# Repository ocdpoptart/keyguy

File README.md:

This entire thing has been a project to make a keyboard that had every quality I liked in one except for having a usb hub (I figured I could make one of those later). Unfortunately this entire thing has spiraled out of control and now I have even learned how to use this silly thing called GitHub. I want to cry.

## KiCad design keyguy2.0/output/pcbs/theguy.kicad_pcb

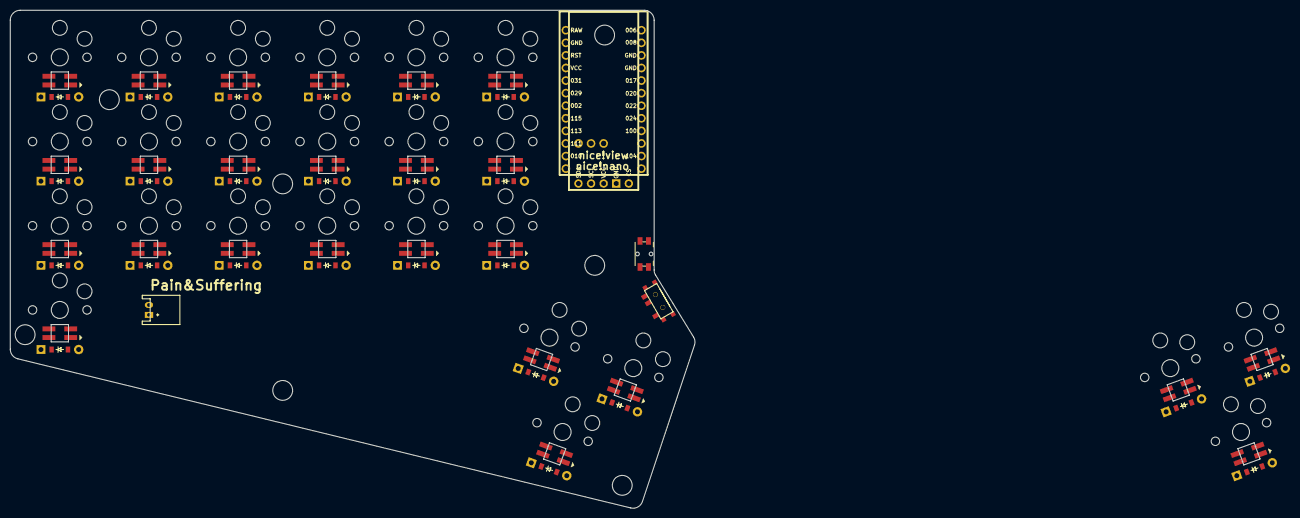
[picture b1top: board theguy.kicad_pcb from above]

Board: 2 copper layers, 255.0 x 100.5 mm, 80 parts (0 on the bottom side), 64 nets, no tracks yet.

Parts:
B1: Panasonic_EVQPUL_EVQPUC
D1, D2, D3, D4, D5, D6, D7, D8, D9, D10, D11, D12, D13, D14, D15, D16, D17, D18, D19, D20, D21, D22, D23, D24, D25: ComboDiode
JST1: JST_PH_S2B-PH-K_02x2.00mm_Angled
LED1, LED2, LED3, LED4, LED5, LED6, LED7, LED8, LED9, LED10, LED11, LED12, LED13, LED14, LED15, LED16, LED17, LED18, LED19, LED20, LED21, LED22, LED23, LED24, LED25: WS2812B
MCU1: nice_nano
S1, S2, S3, S4, S5, S6, S7, S8, S9, S10, S11, S12, S13, S14, S15, S16, S17, S18, S19, S20, S21, S22, S23, S24, S25: PG1350
T1: SPDT_C128955
niceView1: niceView; niceView_headers

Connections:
GND: B1.1, JST1.2, LED1.3, LED2.3, LED3.3, LED4.3, LED5.3, LED6.3, LED7.3, LED8.3, LED9.3, LED10.3, LED11.3, LED12.3, LED13.3, LED14.3, LED15.3, LED16.3, LED17.3, LED18.3, LED19.3, LED20.3, LED21.3, LED22.3, LED23.3, LED24.3, LED25.3, MCU1.3, MCU1.4, MCU1.23, niceView1.2
P002: MCU1.18, S8.1, S9.1, S10.1
P006: LED22.4, LED25.4, MCU1.1
P009: D3.1, D6.1, D9.1, D12.1, D15.1, D18.1, MCU1.13
P010: D4.1, D7.1, D10.1, D13.1, D16.1, D19.1, MCU1.14
P017: MCU1.5, niceView1.5
P020: MCU1.6, niceView1.4
P022: MCU1.7, niceView1.1
P029: MCU1.19, S5.1, S6.1, S7.1
P031: MCU1.20, S1.1, S2.1, S3.1, S4.1
P104: D2.1, D5.1, D8.1, D11.1, D14.1, D17.1, D20.1, D21.1, D23.1, D24.1, MCU1.11
P106: D1.1, D22.1, D25.1, MCU1.12
P111: MCU1.15, S17.1, S18.1, S19.1, S21.1, S22.1, S24.1, S25.1
P113: MCU1.16, S14.1, S15.1, S16.1, S20.1, S23.1
P115: MCU1.17, S11.1, S12.1, S13.1
RAW: MCU1.24, T1.2
RST: B1.2, MCU1.22
VCC: LED1.1, LED2.1, LED3.1, LED4.1, LED5.1, LED6.1, LED7.1, LED8.1, LED9.1, LED10.1, LED11.1, LED12.1, LED13.1, LED14.1, LED15.1, LED16.1, LED17.1, LED18.1, LED19.1, LED20.1, LED21.1, LED22.1, LED23.1, LED24.1, LED25.1, MCU1.21, niceView1.3
extra_cluster: D22.2, S22.2
hell_bottom: D2.2, S2.2
hell_home: D3.2, S3.2
hell_last: D1.2, S1.2
hell_top: D4.2, S4.2
index_bottom: D14.2, S14.2
index_home: D15.2, S15.2
index_top: D16.2, S16.2
inner_bottom: D17.2, S17.2
inner_home: D18.2, S18.2
inner_top: D19.2, S19.2
layer_cluster: D20.2, S20.2
middle_bottom: D11.2, S11.2
middle_home: D12.2, S12.2
middle_top: D13.2, S13.2
mirror_extra_cluster: D25.2, S25.2
mirror_layer_cluster: D23.2, S23.2
mirror_space_cluster: D24.2, S24.2
pinky_bottom: D5.2, S5.2
pinky_home: D6.2, S6.2
pinky_top: D7.2, S7.2
pos: JST1.1, T1.1
rgb_matrix_hell_bottom: LED2.4, LED3.2
rgb_matrix_hell_home: LED3.4, LED4.2
rgb_matrix_hell_last: LED1.4, LED2.2
rgb_matrix_hell_top: LED4.4, LED7.2
rgb_matrix_index_bottom: LED14.4, LED15.2, LED20.2, LED23.2
rgb_matrix_index_home: LED15.4, LED16.2
rgb_matrix_index_top: LED16.4, LED19.2
rgb_matrix_inner_bottom: LED17.4, LED22.2, LED25.2
rgb_matrix_inner_home: LED17.2, LED18.4
rgb_matrix_inner_top: LED18.2, LED19.4
rgb_matrix_middle_home: LED11.2, LED12.4
rgb_matrix_middle_top: LED12.2, LED13.4
rgb_matrix_pinky_bottom: LED5.4, LED8.2
rgb_matrix_pinky_home: LED5.2, LED6.4
rgb_matrix_pinky_top: LED6.2, LED7.4
rgb_matrix_ring_bottom: LED8.4, LED9.2
rgb_matrix_ring_home: LED9.4, LED10.2
rgb_matrix_ring_top: LED10.4, LED13.2
rgb_thumbs_layer_cluster: LED20.4, LED21.2, LED23.4, LED24.2
rgb_thumbs_space_cluster: LED14.2, LED21.4, LED24.4
ring_bottom: D8.2, S8.2
ring_home: D9.2, S9.2
ring_top: D10.2, S10.2
space_cluster: D21.2, S21.2

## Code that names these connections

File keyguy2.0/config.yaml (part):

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            last.skip: true
            bottom:
              led_in: "rgb_{{name}}"
              led_out: rgb_matrix_pinky_home
            home:
              led_in: "rgb_{{name}}"
              led_out: rgb_matrix_pinky_top
            top:
              led_in: "rgb_{{name}}"
              led_out: rgb_matrix_hell_top
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            last.skip: true
            bottom:
              led_in: "rgb_{{name}}"
              led_out: rgb_matrix_pinky_bottom
            home:
              led_in: "rgb_{{name}}"
              led_out: rgb_matrix_ring_bottom
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
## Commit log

2024-09-17 pain and suffering
2024-09-17 simply amazing
2024-09-18 changing things again
2024-09-18 changing things again 2.0
2024-09-19 gonna need to buy a 3d printer at this rate
2024-09-26 future ref
2024-10-04 notes for v2
2025-02-13 2.0 done?
2025-02-15 2.0 done for real this time
2025-02-15 pcbs wired
2025-02-15 pcb files ready to be made
2025-02-16 added a 2.5 for future minor improvements such as correcting screwsize from m2.5 to m2
2025-02-16 created an ideas doc for 2.5
2025-02-16 corrected config so that case has proper depth for battery
2025-02-16 more notes
2025-02-19 corrected cases
2025-02-19 corrected mounting
2025-02-21 fixed leds so all connected and work sad i already sent out 2.0 pcb for production where more than half won't work
2025-02-21 updated ideas to account for fix
2025-02-28 corrected 2.5 so we don't have repeat keys like 2.0, still don't know if leds will work so chill for a bit
